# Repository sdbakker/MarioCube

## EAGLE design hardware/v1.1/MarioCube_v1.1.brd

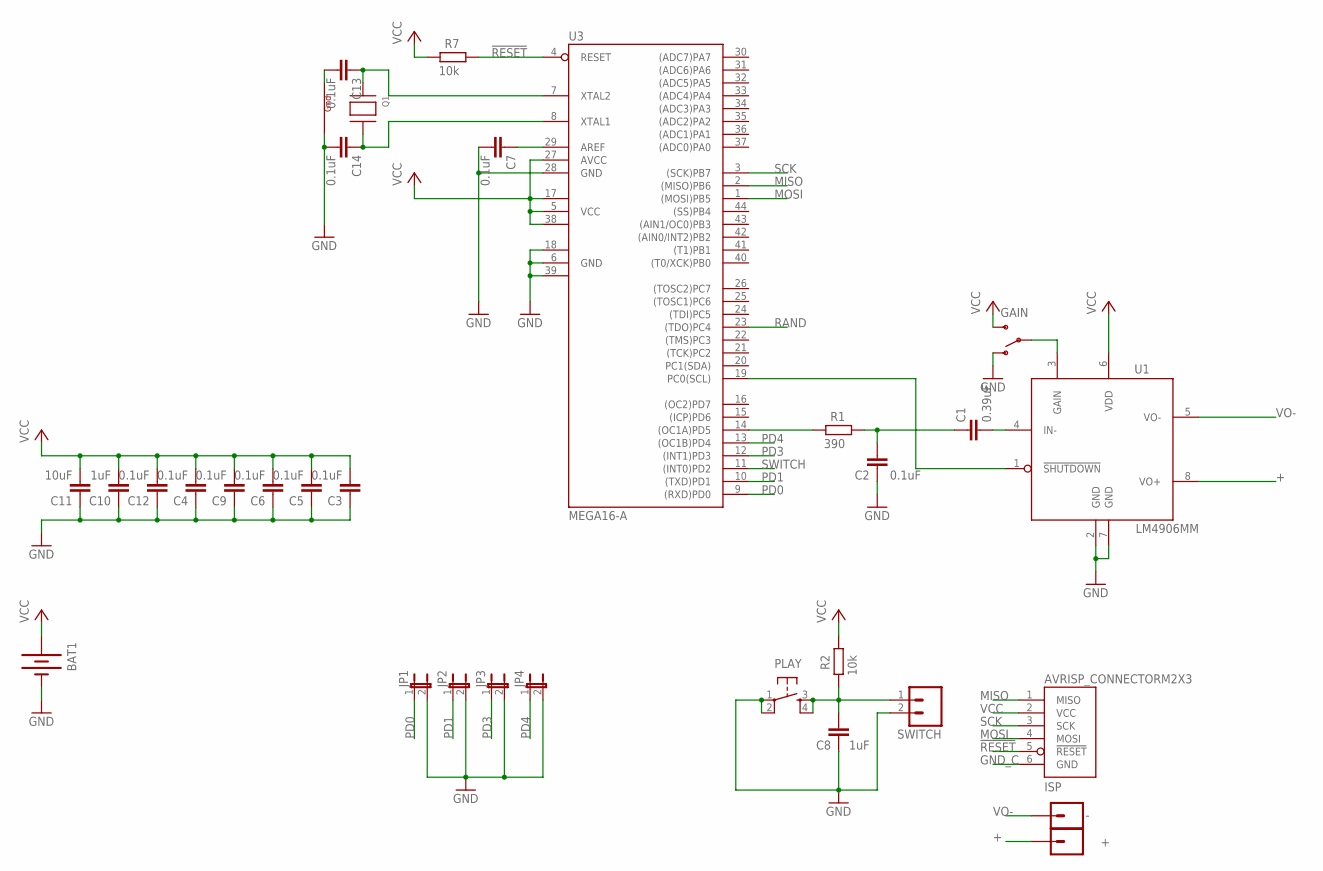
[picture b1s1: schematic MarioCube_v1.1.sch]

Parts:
+: M01OFFSET; 1X01_OFFSET
-: M01OFFSET; 1X01_OFFSET
BAT1: BATTERY2XAAA-2468; BATTERY_HOLDER_2468; DIGIKEY BK-912-CT-ND
C1: 0.39uF; C0603K
C2, C3, C4, C5, C6, C7, C9, C12, C13, C14: 0.1uF; C0603K
C8, C10: 1uF; C0603K
C11: 10uF; C0603K
GAIN: SWITCH-SPSTSMD; AYZ0202; DIGIKEY 401-2013-1-ND
ISP: AVRISP_CONNECTORM2X3; 2X3
JP1, JP2, JP3, JP4: JUMPER-2SMD-NO; SJ_2S-NO
PLAY: TAC_SWITCHSMD; TACTILE_SWITCH_SMD; DIGIKEY CKN9104CT-ND
Q1: XTAL-4-3225; NX3225
R1: 390; R0603
R2, R7: 10k; R0603
SWITCH: M02LOCK; 1X02_LOCK
U1: LM4906MM; MSOP8
U3: MEGA16-A; TQFP44

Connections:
!RESET: ISP.5 (!RESET), R7.1, U3.4 (RESET)
+: +.1, U1.8 (VO+)
GND_C: BAT1.GND@1 (-), C2.1, C3.1, C4.1, C5.1, C6.1, C7.2, C8.1, C9.1, C10.1, C11.1, C12.1, C13.2, C14.2, GAIN.1 (O), ISP.6 (GND), JP1.2, JP2.2, JP3.2, JP4.2, PLAY.1, PLAY.2, Q1.2 (G2), Q1.4 (G1), SWITCH.2, U1.2 (GND), U1.7 (GND), U3.6 (GND), U3.18 (GND1), U3.28 (GND), U3.39 (GND2)
MISO: ISP.1 (MISO), U3.2 ((MISO)PB6)
MOSI: ISP.4 (MOSI), U3.1 ((MOSI)PB5)
unnamed: C1.2, U1.4 (IN-)
unnamed: U1.1 (!SHUTDOWN), U3.19 (PC0(SCL))
unnamed: C1.1, C2.2, R1.1
unnamed: GAIN.2, U1.3 (GAIN)
unnamed: R1.2, U3.14 ((OC1A)PD5)
unnamed: C14.1, Q1.3 (X2), U3.8 (XTAL1)
unnamed: C13.1, Q1.1 (X1), U3.7 (XTAL2)
unnamed: C7.1, U3.29 (AREF)
PD0: JP1.1, U3.9 ((RXD)PD0)
PD1: JP2.1, U3.10 ((TXD)PD1)
PD3: JP3.1, U3.12 ((INT1)PD3)
PD4: JP4.1, U3.13 ((OC1B)PD4)
RAND: U3.23 ((TDO)PC4)
SCK: ISP.3 (SCK), U3.3 ((SCK)PB7)
SWITCH: C8.2, PLAY.3, PLAY.4, R2.2, SWITCH.1, U3.11 ((INT0)PD2)
VCC: BAT1.PWR@1 (+), C3.2, C4.2, C5.2, C6.2, C9.2, C10.2, C11.2, C12.2, GAIN.3 (S), ISP.2 (VCC), R2.1, R7.2, U1.6 (VDD), U3.5 (VCC), U3.17 (VCC1), U3.27 (AVCC), U3.38 (VCC2)
VO-: -.1, U1.5 (VO-)

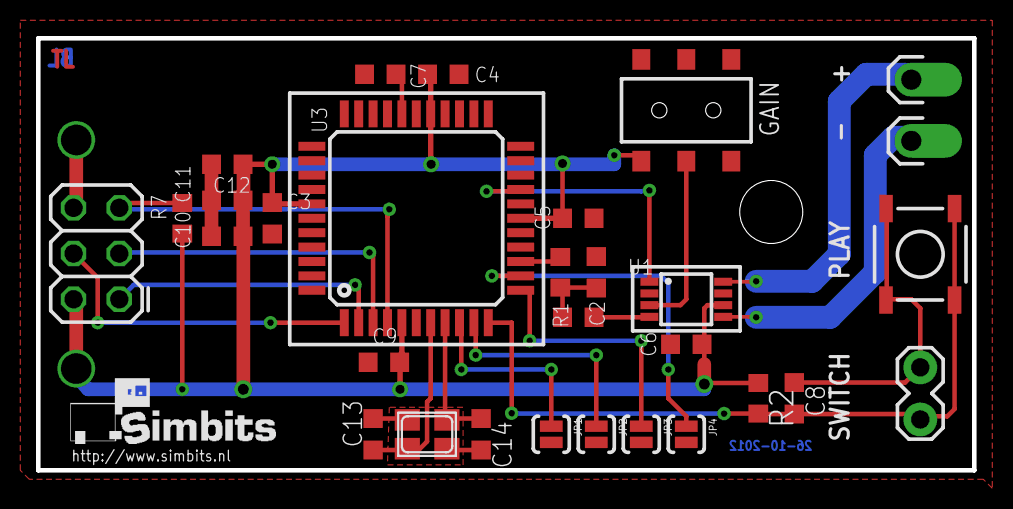
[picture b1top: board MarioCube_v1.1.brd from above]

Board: 2 copper layers, 52.0 x 24.0 mm, 31 parts (1 on the bottom side), 21 nets.
